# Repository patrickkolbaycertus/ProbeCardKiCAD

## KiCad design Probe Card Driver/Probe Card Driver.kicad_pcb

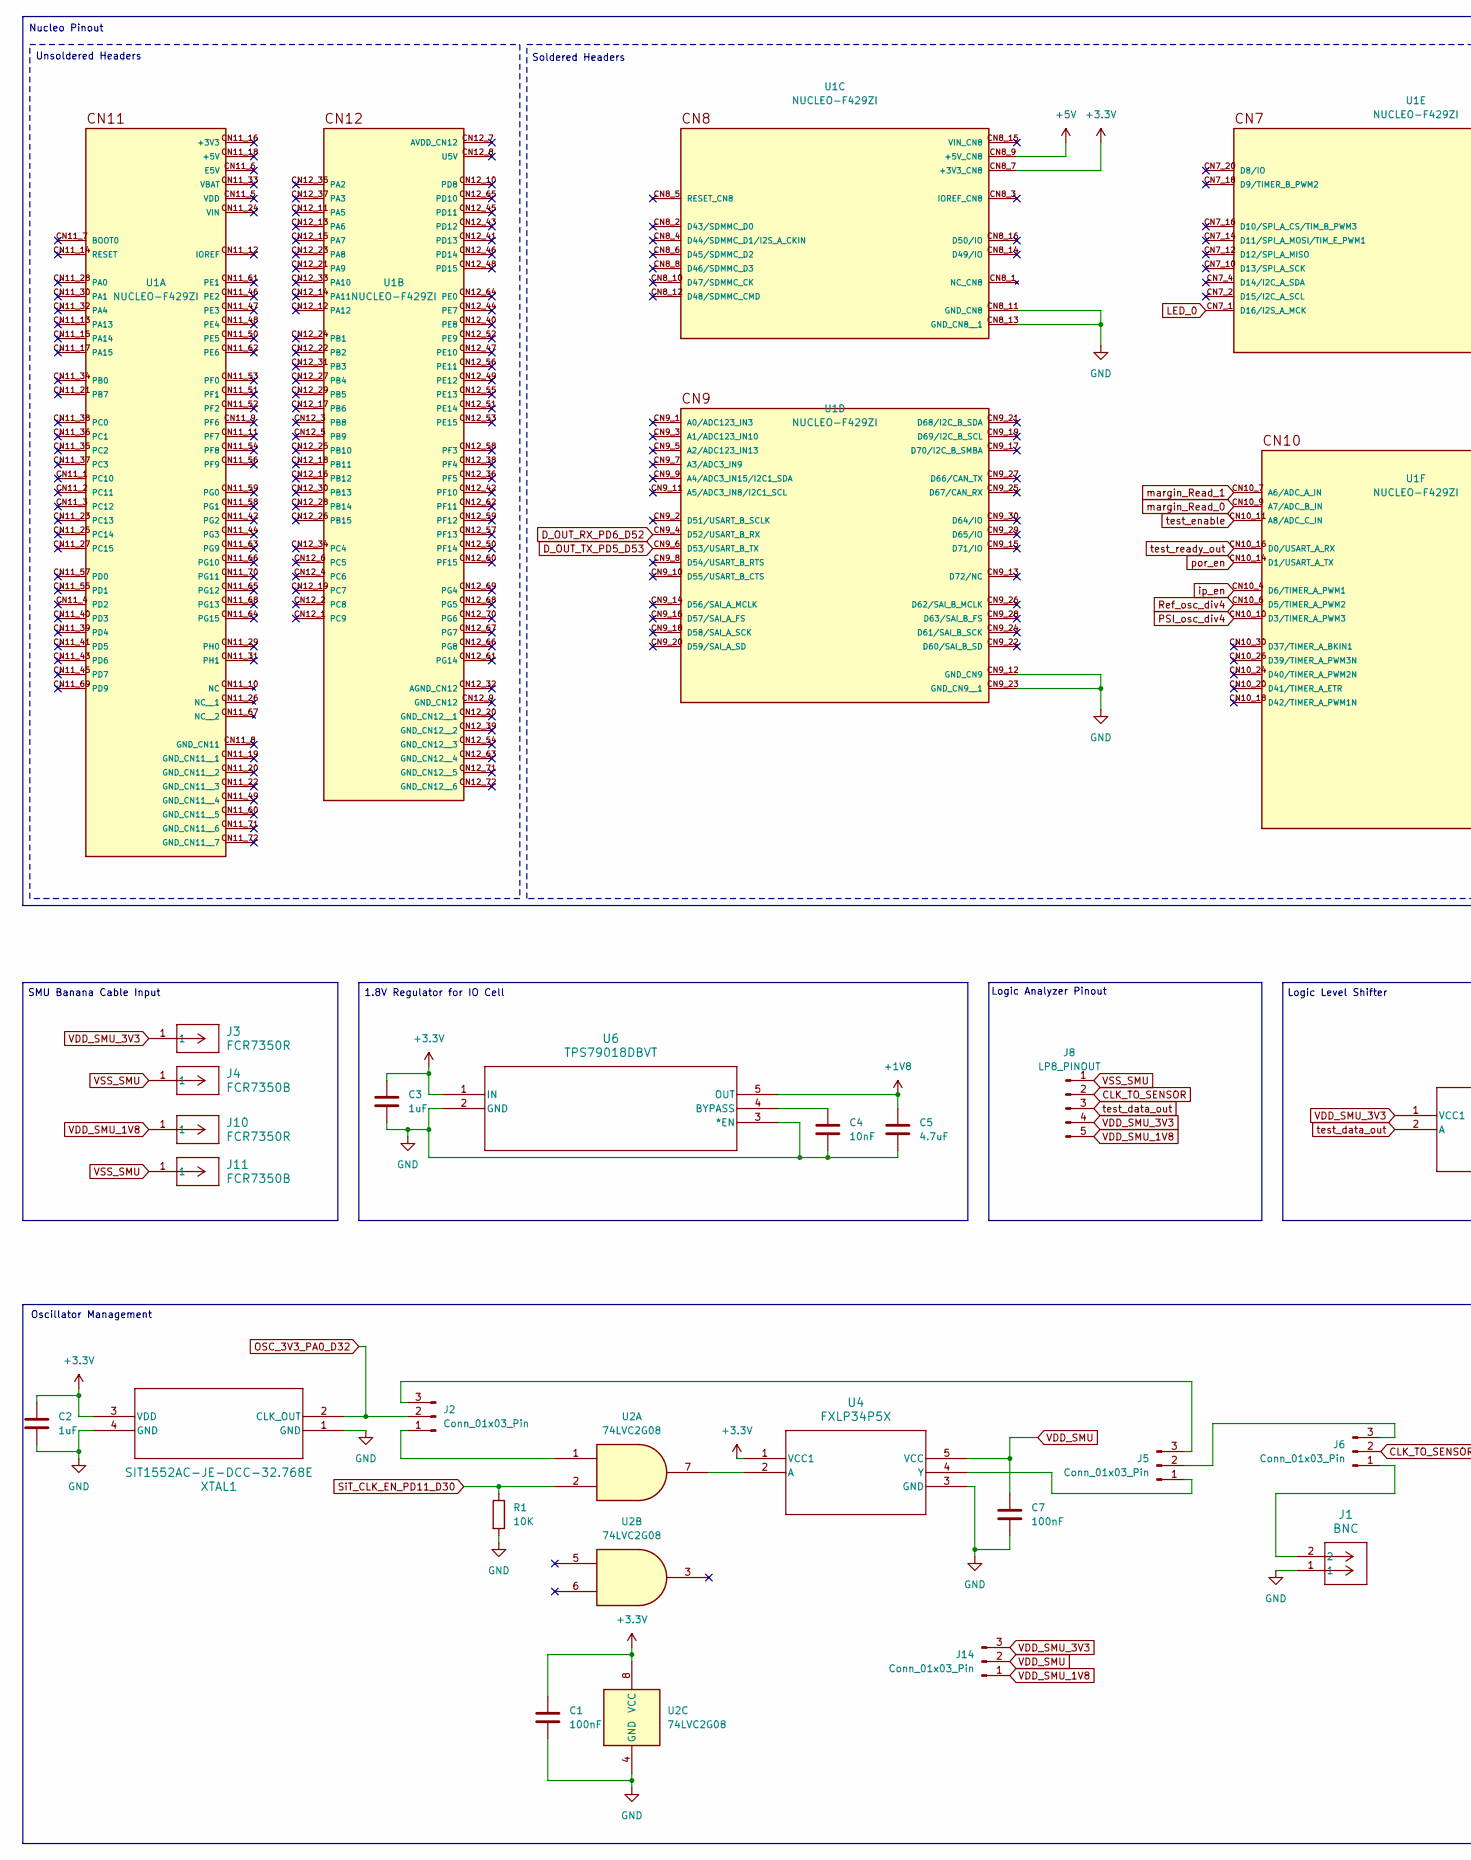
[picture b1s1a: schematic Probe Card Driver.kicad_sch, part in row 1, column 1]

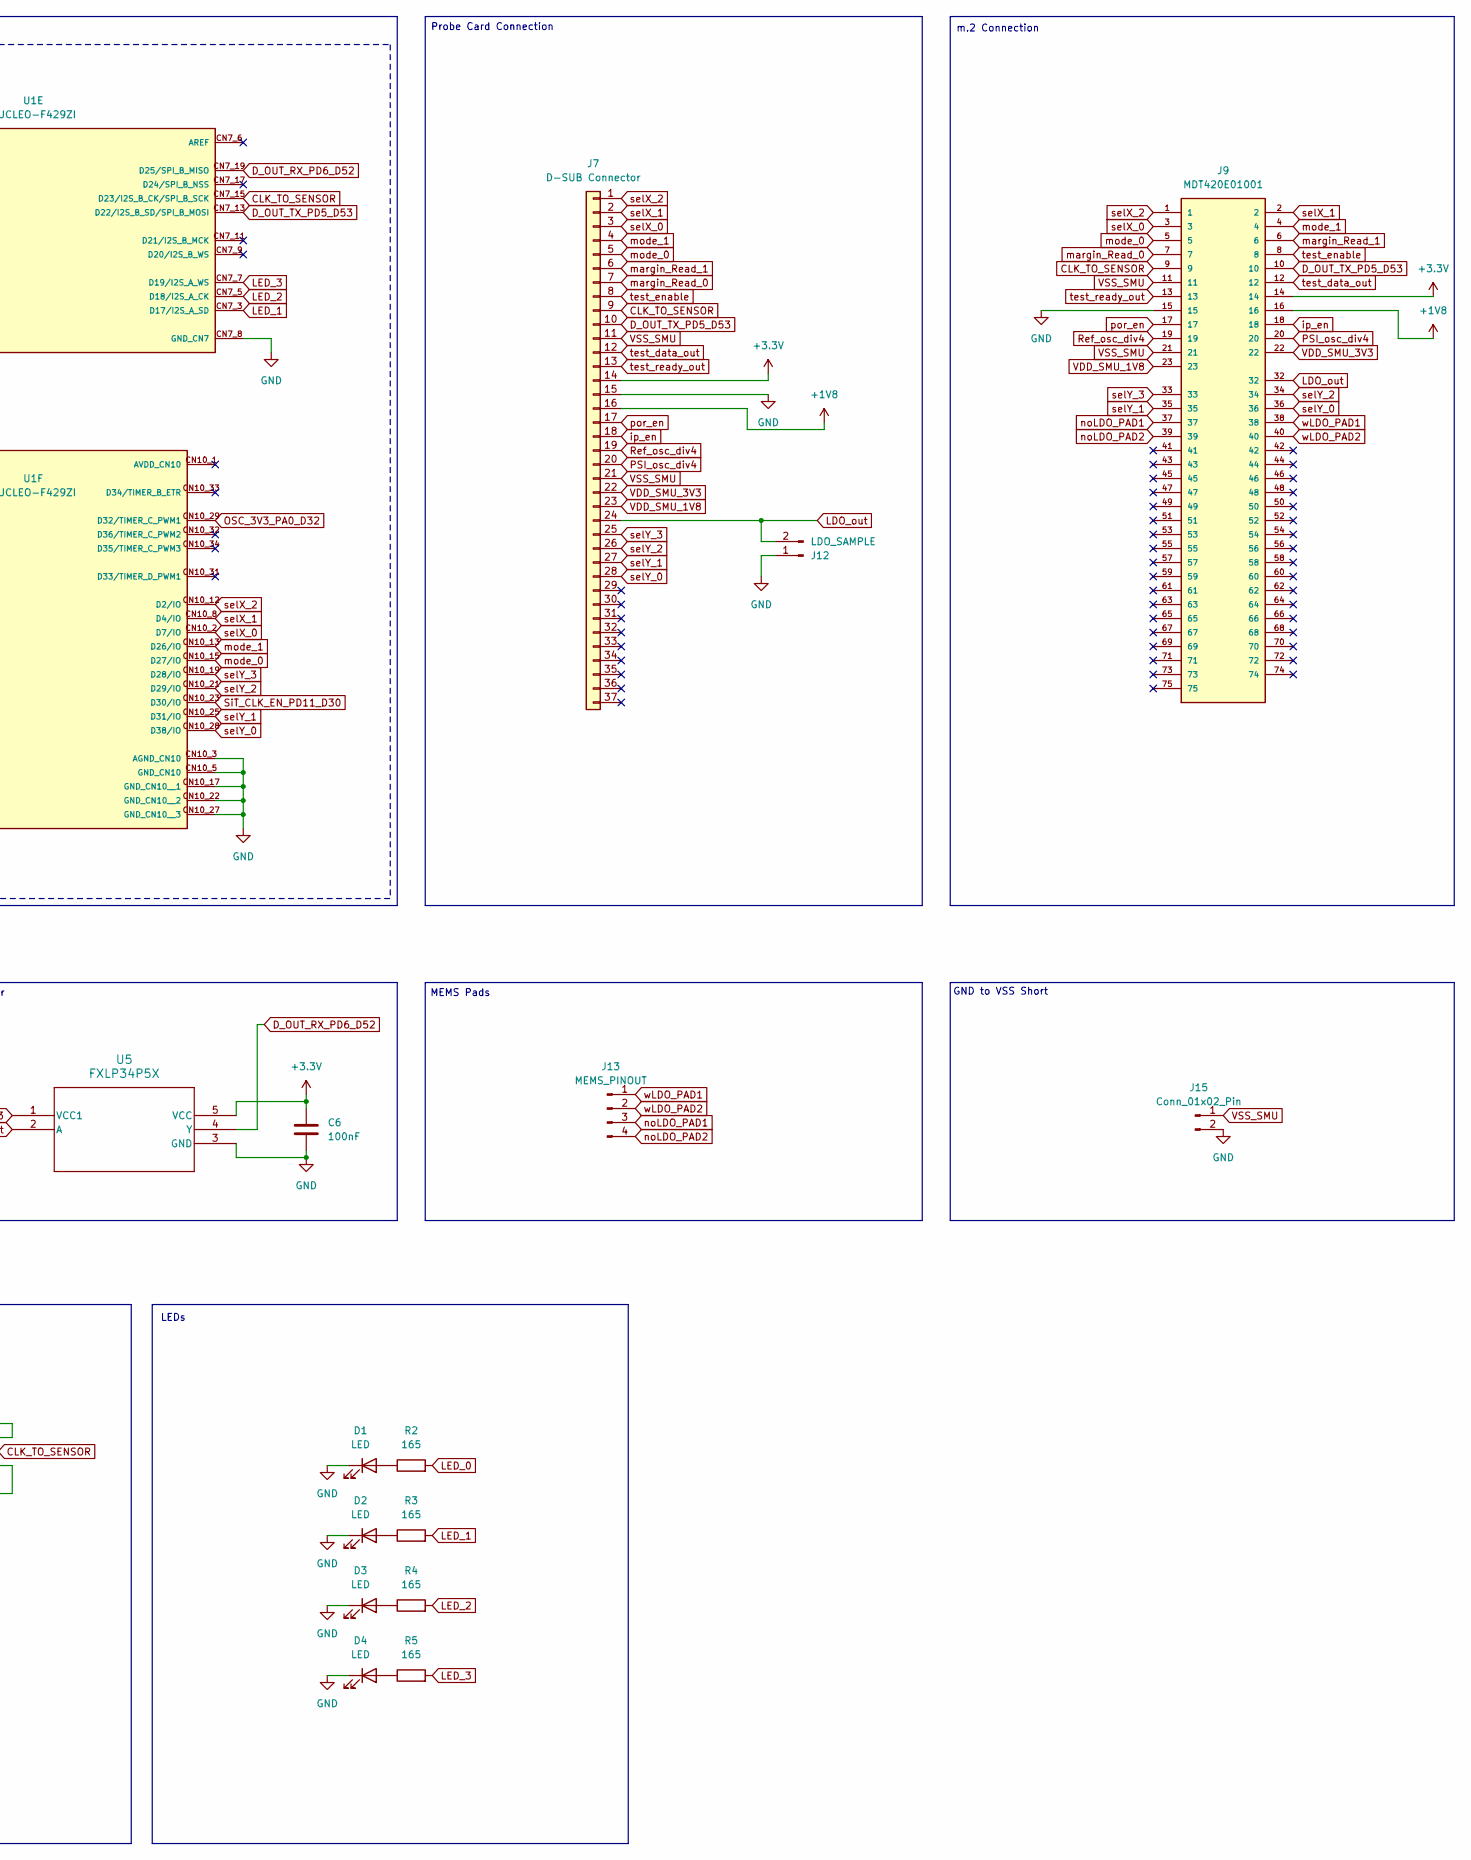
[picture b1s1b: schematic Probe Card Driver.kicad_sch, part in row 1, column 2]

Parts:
C1, C6, C7: 100nF; C_0603_1608Metric
C2, C3: 1uF; C_0603_1608Metric
C4: 10nF; C_0603_1608Metric
C5: 4.7uF; C_0603_1608Metric
D1, D2, D3, D4: LED; LED_0603_1608Metric
J1: BNC; CONN_CONBN_LNX
J2, J5, J6, J14: Conn_01x03_Pin; PinHeader_1x03_P2.54mm_Vertical
J3, J10: FCR7350R; CONN1_FCR7350R_CLF
J4, J11: FCR7350B; CONN1_FCR7350R_CLF
J7: D-SUB Connector; D37P33E4GX00LF
J8: LP8_PINOUT; PinSocket_1x05_P2.54mm_Vertical
J9: MDT420E01001; M.2-CONNECTOR-E; PARTREV 7
J12: LDO_SAMPLE; PinSocket_1x02_P2.54mm_Vertical
J13: MEMS_PINOUT; PinSocket_1x04_P2.54mm_Vertical
J15: Conn_01x02_Pin; PinHeader_1x02_P2.54mm_Vertical
R1: 10K; R_0603_1608Metric
R2, R3, R4, R5: 165; R_0603_1608Metric
U1: NUCLEO-F429ZI; MODULE_NUCLEO-F429ZI; PARTREV 8
U2: 74LVC2G08; DCU8
U4, U5: FXLP34P5X; SC70-5_2P2X1P3_ONS
U6: TPS79018DBVT; DBV5
XTAL1: SIT1552AC-JE-DCC-32.768E; BGA4_SiT1532_SIT

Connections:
+1V8: C5.1, J7.16, J9.16, U6.5 (OUT)
+3.3V: C1.1, C2.1, C3.1, C6.1, J7.14, J9.14, U1.CN8_7 (+3V3_CN8), U2.8 (VCC), U4.1 (VCC1), U5.5 (VCC), U6.1 (IN), XTAL1.3 (VDD)
+5V: U1.CN8_9 (+5V_CN8)
CLK_TO_SENSOR: J6.2, J7.9, J8.2, J9.9, U1.CN7_15 (D23/I2S_B_CK/SPI_B_SCK)
D_OUT_RX_PD6_D52: U1.CN7_19 (D25/SPI_B_MISO), U1.CN9_4 (D52/USART_B_RX), U5.4 (Y)
D_OUT_TX_PD5_D53: J7.10, J9.10, U1.CN7_13 (D22/I2S_B_SD/SPI_B_MOSI), U1.CN9_6 (D53/USART_B_TX)
GND: C1.2, C2.2, C3.2, C4.2, C5.2, C6.2, C7.2, D1.1 (K), D2.1 (K), D3.1 (K), D4.1 (K), J1.1, J7.15, J9.15, J12.1, J15.2, R1.2, U1.CN7_8 (GND_CN7), U1.CN8_11 (GND_CN8), U1.CN8_13 (GND_CN8__1), U1.CN9_12 (GND_CN9), U1.CN9_23 (GND_CN9__1), U1.CN10_3 (AGND_CN10), U1.CN10_5 (GND_CN10), U1.CN10_17 (GND_CN10__1), U1.CN10_22 (GND_CN10__2), U1.CN10_27 (GND_CN10__3), U2.4 (GND), U4.3 (GND), U5.3 (GND), U6.2 (GND), U6.3 (*EN), XTAL1.1 (GND), XTAL1.4 (GND)
LDO_out: J7.24, J9.32, J12.2
LED_0: R2.2, U1.CN7_1 (D16/I2S_A_MCK)
LED_1: R3.2, U1.CN7_3 (D17/I2S_A_SD)
LED_2: R4.2, U1.CN7_5 (D18/I2S_A_CK)
LED_3: R5.2, U1.CN7_7 (D19/I2S_A_WS)
unnamed: D1.2 (A), R2.1
unnamed: D2.2 (A), R3.1
unnamed: D3.2 (A), R4.1
unnamed: D4.2 (A), R5.1
unnamed: J2.1, U2.1
unnamed: J2.3, J5.3
unnamed: J5.1, U4.4 (Y)
unnamed: J5.2, J6.3
unnamed: J1.2, J6.1
unnamed: U2.7, U4.2 (A)
unnamed: C4.1, U6.4 (BYPASS)
OSC_3V3_PA0_D32: J2.2, U1.CN10_29 (D32/TIMER_C_PWM1), XTAL1.2 (CLK_OUT)
PSI_osc_div4: J7.20, J9.20, U1.CN10_10 (D3/TIMER_A_PWM3)
Ref_osc_div4: J7.19, J9.19, U1.CN10_6 (D5/TIMER_A_PWM2)
SiT_CLK_EN_PD11_D30: R1.1, U1.CN10_23 (D30/IO), U2.2
VDD_SMU: C7.1, J14.2, U4.5 (VCC)
VDD_SMU_1V8: J7.23, J8.5, J9.23, J10.1, J14.1
VDD_SMU_3V3: J3.1, J7.22, J8.4, J9.22, J14.3, U5.1 (VCC1)
VSS_SMU: J4.1, J7.11, J7.21, J8.1, J9.11, J9.21, J11.1, J15.1
ip_en: J7.18, J9.18, U1.CN10_4 (D6/TIMER_A_PWM1)
margin_Read_0: J7.7, J9.7, U1.CN10_9 (A7/ADC_B_IN)
margin_Read_1: J7.6, J9.6, U1.CN10_7 (A6/ADC_A_IN)
mode_0: J7.5, J9.5, U1.CN10_15 (D27/IO)
mode_1: J7.4, J9.4, U1.CN10_13 (D26/IO)
noLDO_PAD1: J9.37, J13.3
noLDO_PAD2: J9.39, J13.4
por_en: J7.17, J9.17, U1.CN10_14 (D1/USART_A_TX)
selX_0: J7.3, J9.3, U1.CN10_2 (D7/IO)
selX_1: J7.2, J9.2, U1.CN10_8 (D4/IO)
selX_2: J7.1, J9.1, U1.CN10_12 (D2/IO)
selY_0: J7.28, J9.36, U1.CN10_28 (D38/IO)
selY_1: J7.27, J9.35, U1.CN10_25 (D31/IO)
selY_2: J7.26, J9.34, U1.CN10_21 (D29/IO)
selY_3: J7.25, J9.33, U1.CN10_19 (D28/IO)
test_data_out: J7.12, J8.3, J9.12, U5.2 (A)
test_enable: J7.8, J9.8, U1.CN10_11 (A8/ADC_C_IN)
test_ready_out: J7.13, J9.13, U1.CN10_16 (D0/USART_A_RX)
wLDO_PAD1: J9.38, J13.1
wLDO_PAD2: J9.40, J13.2

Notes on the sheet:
Unsoldered Headers
Soldered Headers
1.8V Regulator for IO Cell
LEDs
MEMS Pads
Oscillator Management
Nucleo Pinout
Logic Analyzer Pinout
m.2 Connection
Logic Level Shifter
Probe Card Connection
SMU Banana Cable Input
GND to VSS Short

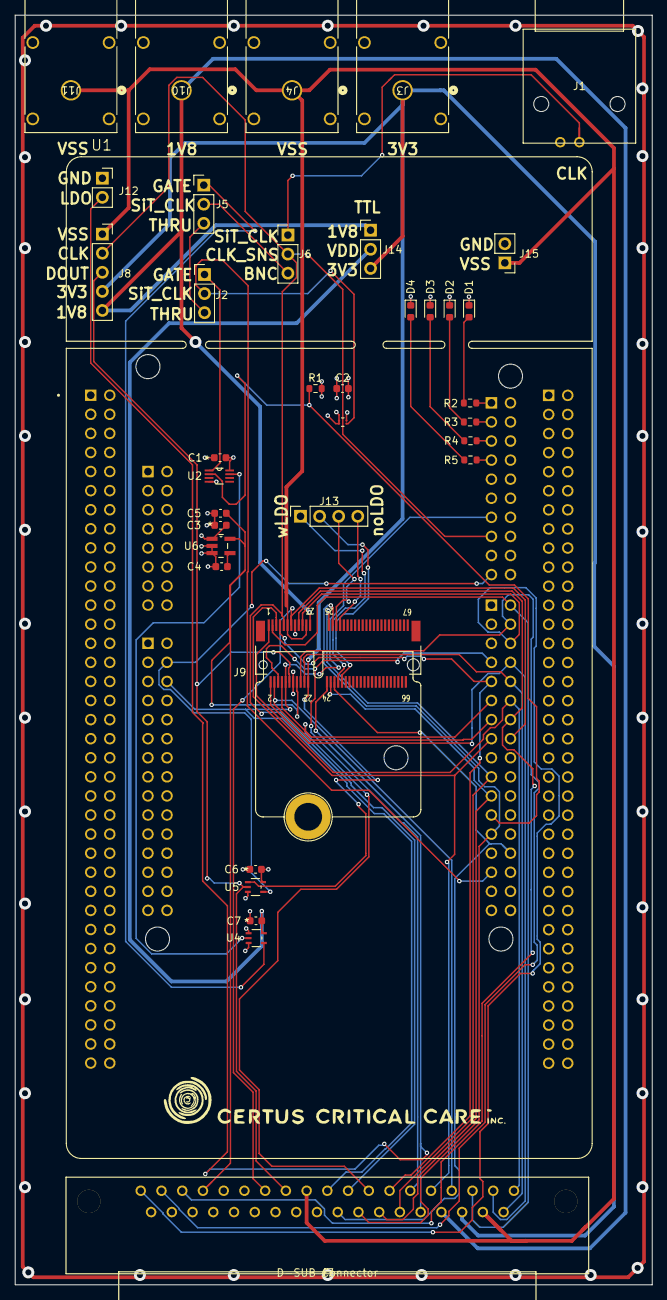
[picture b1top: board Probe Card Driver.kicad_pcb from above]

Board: 4 copper layers, 84.8 x 169.0 mm, 37 parts (0 on the bottom side), 50 nets.

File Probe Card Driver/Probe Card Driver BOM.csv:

Reference,Value,Datasheet,Digikey PN,Footprint,Qty,DNP
"C1,C6,C7",100nF,https://mm.digikey.com/Volume0/opasdata/d220001/medias/docus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,1276-1005-1-ND,Capacitor_SMD:C_0603_1608Metric,3,
"C2,C3",1uF,https://weblib.samsungsem.com/mlcc/mlcc-ec-data-sheet.do?par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,1276-1019-1-ND,Capacitor_SMD:C_0603_1608Metric,2,
C4,10nF,https://mm.digikey.com/Volume0/opasdata/d220001/medias/docus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,1276-1009-1-ND,Capacitor_SMD:C_0603_1608Metric,1,
C5,4.7uF,https://mm.digikey.com/Volume0/opasdata/d220001/medias/docus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,1276-1784-1-ND,Capacitor_SMD:C_0603_1608Metric,1,
"D1,D4",LED,https://www.we-online.com/components/products/datasheet/1500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,732-4979-1-ND,LED_SMD:LED_0603_1608Metric,2,
D2,LED,https://www.we-online.com/components/products/datasheet/1500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,732-4980-1-ND,LED_SMD:LED_0603_1608Metric,1,
D3,LED,https://www.we-online.com/components/products/datasheet/1500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,732-4981-1-ND,LED_SMD:LED_0603_1608Metric,1,
J1,BNC,https://www.te.com/commerce/DocumentDelivery/DDEController?A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,343-CONBNC002-ND,InHouseFootprints:CONN_CONBN_LNX,1,
"J2,J5,J6,J14",Conn_01x03_Pin,~,No Stuff,Connector_PinHeader_2.54mm:PinHeader_1x03_P2.54mm_Vertical,4,
"J3,J10",FCR7350R,FCR7350R,4654-FCR7350R-ND,InHouseFootprints:CONN1_FCR7350R_CLF,2,
"J4,J11",FCR7350B,FCR7350B,4654-FCR7350B-ND,InHouseFootprints:CONN1_FCR7350R_CLF,2,
J7,D-SUB Connector,https://mm.digikey.com/Volume0/opasdata/d220001/medias/docus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,609-5416-ND,InHouseFootprints:D37P33E4GX00LF,1,
J8,LP8_PINOUT,~,No Stuff,Connector_PinSocket_2.54mm:PinSocket_1x05_P2.54mm_Vertical,1,
J9,MDT420E01001,https://cdn.amphenol-cs.com/media/wysiwyg/files/documentatio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,MDT420E01001CT-ND,InHouseFootprints:M.2-CONNECTOR-E,1,
J12,LDO_SAMPLE,~,No Stuff,Connector_PinSocket_2.54mm:PinSocket_1x02_P2.54mm_Vertical,1,
J13,MEMS_PINOUT,~,No Stuff,Connector_PinSocket_2.54mm:PinSocket_1x04_P2.54mm_Vertical,1,
J15,Conn_01x02_Pin,~,No Stuff,Connector_PinHeader_2.54mm:PinHeader_1x02_P2.54mm_Vertical,1,
R1,10K,https://mm.digikey.com/Volume0/opasdata/d220001/medias/docus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,1276-3485-1-ND,Resistor_SMD:R_0603_1608Metric,1,
"R2,R3,R4,R5",165,https://mm.digikey.com/Volume0/opasdata/d220001/medias/docus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,1276-4576-1-ND,Resistor_SMD:R_0603_1608Metric,4,
U1,NUCLEO-F429ZI,,No Stuff,InHouseFootprints:MODULE_NUCLEO-F429ZI,1,
U2,74LVC2G08,http://www.ti.com/lit/sg/scyt129e/scyt129e.pdf,FXLP34P5XCT-ND,InHouseFootprints:DCU8,1,
"U4,U5",FXLP34P5X,https://www.onsemi.com/pdf/datasheet/fxlp34-d.pdf,FXLP34P5XCT-ND,InHouseFootprints:SC70-5_2P2X1P3_ONS,2,
U6,TPS79018DBVT,https://www.ti.com/general/docs/suppproductinfo.tsp?distId=1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,296-TPS79018DBVTCT-ND,InHouseFootprints:DBV5,1,
XTAL1,SIT1552AC-JE-DCC-32.768E,https://www.sitime.com/datasheet/SiT1552,1473-1374-1-ND,InHouseFootprints:BGA4_SiT1532_SIT,1,

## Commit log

2024-08-28 Add files via upload
    Initial commit
2024-08-28 Added BOM and Minor Updates
    Added a BOM and included minor updates to layout and schematic.

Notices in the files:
parts and their libraries:
Copyright 2016 Accelerated Designs. All rights reserved.
